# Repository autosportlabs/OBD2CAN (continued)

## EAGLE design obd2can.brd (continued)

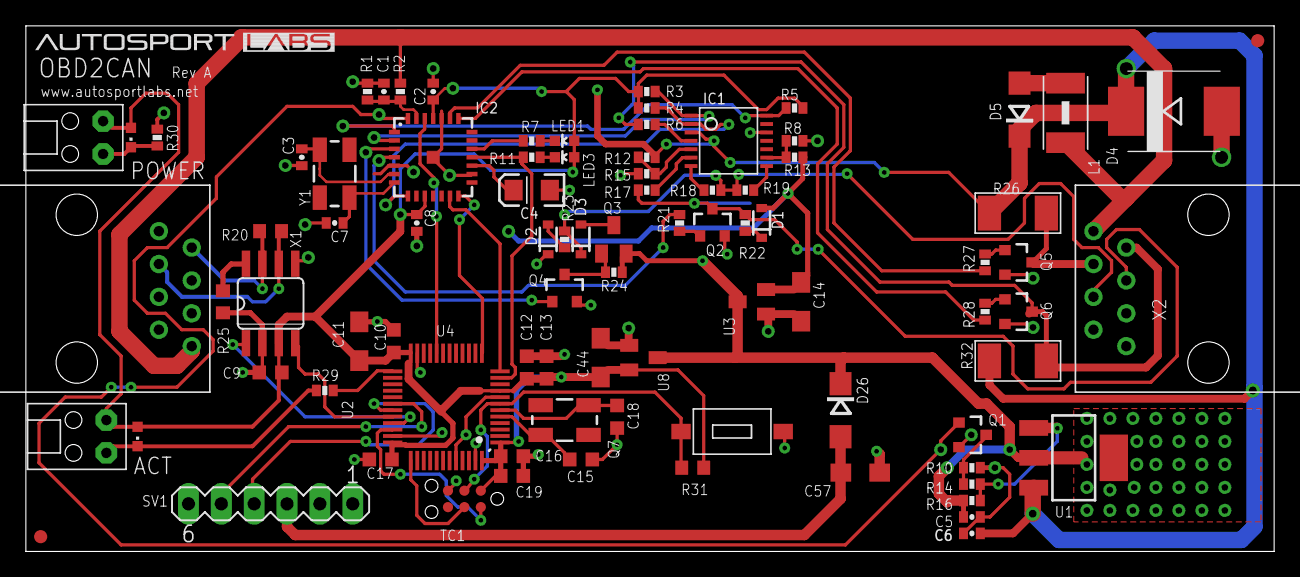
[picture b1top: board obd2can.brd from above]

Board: 2 copper layers, 96.5 x 40.6 mm, 85 parts (0 on the bottom side), 61 nets.

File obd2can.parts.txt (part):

Partlist


EAGLE Version 7.2.0 Copyright (c) 1988-2014 CadSoft

Assembly variant: 

Part     Value                            Device                           Package                           Library           Sheet

ACT      PANEL_LED                        PANEL_LED                        RIGHTANGLE_CML_5323F5             LEDs              1
ACT_S                                     LEDCHIPLED_0603                  CHIPLED_0603                      led               1
C1       0.1uF                            CAP0402-CAP                      0402-CAP                          SparkFun          3
C2       1uF                              CAP0402-CAP                      0402-CAP                          SparkFun          3
C3       27pF                             CAP0402-CAP                      0402-CAP                          SparkFun          3
C4       10uF ESR<=5                      CAP_POL1206                      EIA3216                           SparkFun          3
C5       1uF                              CAP0402-CAP                      0402-CAP                          SparkFun          2
C6       0.1uF                            CAP0402-CAP                      0402-CAP                          SparkFun          2
C7       27pF                             CAP0402-CAP                      0402-CAP                          SparkFun          3
C8       1uF                              CAP0402-CAP                      0402-CAP                          SparkFun          3
C9       0.1uf                            C-USC0603K                       C0603K                            rcl               1
C10      0.1uf                            C-USC0603K                       C0603K                            rcl               1
C11      10uF                             CPOL-USSMCA                      SMC_A                             rcl               1
C12      4.7uf                            C-USC0603K                       C0603K                            rcl               1
C13      0.01uf                           C-USC0603K                       C0603K                            rcl               1
C14      10uF                             CPOL-USSMCA                      SMC_A                             rcl               2
C15      0.1uf                            C-USC0603K                       C0603K                            rcl               1
C16      0.1uf                            C-USC0603K                       C0603K                            rcl               1
C17      4.7uf                            C-USC0603K                       C0603K                            rcl               1
C18      0.1uf                            C-USC0603K                       C0603K                            rcl               1
C19      1uf                              C-USC0603K                       C0603K                            rcl               1
C44      10uF                             CPOL-USSMCA                      SMC_A                             rcl               2
C57      10uF                             CPOL-USSMCA                      SMC_A                             rcl               1
D1       BAS16                            DIODESOD                         SOD-323                           SparkFun          4
D2       BAS16                            DIODESOD                         SOD-323                           SparkFun          4
D3       BAS16                            DIODESOD                         SOD-323                           SparkFun          4
D4                                        SCHOTTKY-DIODESMC                SMC                               diode             2
D5       400V 1A                          DIODE1                           SMA                               smt_diodes        2
D26      SCHOTTKY                         SCHOTTKY                         SMA                               smt_diodes        1
IC1      LM339PWR                         LM339PWR                         TSSOP-14                          _stn_logic        4
IC2      SCANTOOL                         SCANTOOL                         _STN_SCANTOOL_QFN-28-S            SparkFun          3
L1                                        WE-CBF_1812                      1812                              wuerth-elektronik 2
LED1     YELLOW                           LED0603                          LED-0603                          SparkFun          3
LED3     RED                              LED0603                          LED-0603                          SparkFun          3
POWER    PANEL_LED                        PANEL_LED                        RIGHTANGLE_CML_5323F5             LEDs              2
POWER_S                                   LEDCHIPLED_0603                  CHIPLED_0603                      led               2
Q1       BSS138                           MOSFET-NCHANNELSMD               SOT23-3                           SparkFun          2
Q2       MMBT2222                         TRANSISTOR_NPNSOT23-3            SOT23-3                           SparkFun          4
Q3       ZXMP6A13FTA                      MOSFET-PCHANNEL                  SOT23                             SparkFun          4
Q4       BSS138                           MOSFET-NCHANNELSMD               SOT23-3                           SparkFun          4
Q5       MMBT2222                         TRANSISTOR_NPNSOT23-3            SOT23-3                           SparkFun          4
Q6       MMBT2222                         TRANSISTOR_NPNSOT23-3            SOT23-3                           SparkFun          4
Q7       8MHz                             CRYSTAL5X3                       CRYSTAL-SMD-5X3                   SparkFun2         1
R1       10K                              RESISTOR0402-RES                 0402-RES                          SparkFun          3
R2       62K                              RESISTOR0402-RES                 0402-RES                          SparkFun          3
R3       10k                              RESISTOR0402-RES                 0402-RES                          SparkFun          4
R4       10k                              RESISTOR0402-RES                 0402-RES                          SparkFun          4
R5       10k                              RESISTOR0402-RES                 0402-RES                          SparkFun          4
R6       10k                              RESISTOR0402-RES                 0402-RES                          SparkFun          4
R7       330                              RESISTOR0402-RES                 0402-RES                          SparkFun          3
R8       4.7k                             RESISTOR0402-RES                 0402-RES                          SparkFun          4
R10      374                              RESISTOR0402-RES                 0402-RES                          SparkFun          2
R11      330                              RESISTOR0402-RES                 0402-RES                          SparkFun          3
R12      10k                              RESISTOR0402-RES                 0402-RES                          SparkFun          4
R13      1.2k                             RESISTOR0402-RES                 0402-RES                          SparkFun          4
R14      866                              RESISTOR0402-RES                 0402-RES                          SparkFun          2
R15      10k                              RESISTOR0402-RES                 0402-RES                          SparkFun          4
R16      240                              RESISTOR0402-RES                 0402-RES                          SparkFun          2
R17      10k                              RESISTOR0402-RES                 0402-RES                          SparkFun          4
R18      10k                              RESISTOR0402-RES                 0402-RES                          SparkFun          4
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
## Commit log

2014-02-16 added initial files and license
2014-02-18 added swdebug and boot button
2014-02-18 minor label updates
2014-02-19 grounded vref pin on can transceiver
2014-05-14 added image
2014-05-14 updated readme with improved description and board screenshot
2015-06-05 OBD2CAN WIP
2015-06-06 combined designs together
2015-06-06 label adjustment, snapshot image
2015-06-09 OBD2CAN WIP - more air wires routed
2015-06-09 only 5 more airwires to route...
2015-06-09 fully routed; passes DRC and ERC
2015-06-09 added the ability to supply power via FTDI header
2015-06-11 Fixed typo
2015-06-25 add NVM_RST line between STM32 and STN chips
2015-06-25 updated board image
2015-06-26 Add script to render PNGs of schematics, boards, and part list
2015-06-26 fix palette in rendered images, link to correct board image in readme
2016-02-01 cleaned up old files
2016-02-01 upate readme
2016-07-12 removed obsolete CAD files
2016-07-12 updated ignore file
2016-07-12 initial firmware load
2016-07-13 WIP for talking to STN1110
2016-07-15 WIP, update ChibiOS, update STN1110 reset
2016-07-15 update new ChibiOS
2016-07-15 update license
2016-07-17 more updates
2016-07-17 add license
2016-08-29 WIP enabling CAN
2016-08-30 WIP for CAN
2016-08-31 tweak baud rate for 500K. may not be accurate b/c internal oscillator
2016-08-31 set message length
2016-08-31 minor refactoring
2016-08-31 beginnings of CAN command message handling
2016-08-31 refactored debug writing
2016-08-31 WIP receiving PID requests
2016-09-01 bare end-end functionality; very WIP
2016-09-01 correct PID translation into CAN
2016-09-01 major refactoring
2016-09-01 documentation.
2016-09-01 refactor serial initialization
2016-09-01 updated commenting
2016-09-01 pass through OBDII request transparently, allowing any PID or mode
2016-09-01 expand heap
2016-09-01 proper timing for CAN messages and delays
2016-09-01 enable HSE.. maybe?
2016-09-01 set runtime STN1110 baud rate
2016-09-02 added logging infrastructure and other refactoring
2016-09-02 removed unused file
2016-09-02 clarified control message
2016-09-02 added license headers
2016-09-02 removed unused files
2016-09-02 removed unsused files
2016-09-02 remove unused files
2016-09-02 formatting
2016-09-02 extracted magic values; documentation
2016-09-02 refactored thread creation
2016-09-02 added watchdog support; disabled for now
2016-09-02 handle invalid pids; add metrics for stn1110
2016-09-02 refactored logging
2016-09-02 update CAN control ID
2016-09-02 added more error handling and tracking
2016-09-02 controllable reset and protocol via can message
2016-09-02 enum for obdii protocols
2016-09-03 enabled adaptive timing and timeout parameters
2016-09-03 added stats broadcasting
2016-09-03 make DLC length for stats 8 bytes
2016-09-03 restore logging level
2016-09-03 key off of > prompt for returned data
2016-09-04 enable adaptive stretching of OBDII requests to accomodate slower protocols
2016-09-06 better detect BUS ??? ERROR messages
2016-09-06 cap max bytes in message to CAN message length - 1
2016-09-18 add brief logging and timestamp support
2016-09-18 switch to 250K baud for CAN
2016-09-18 refactored to have STN1110 pid request in STN1110.c
2016-09-18 detect protocol after first successful PID response; various other refactorings
2016-09-19 simplify error handling; reset system if there are excessive errors
2016-09-19 disable automatic CAN message re-transmit
2016-09-19 enhanced documentation
2016-09-19 update README with more documentation
2016-09-19 formatted with astyle --linux
2016-09-19 fix markdown
2016-09-19 update git ignore
2016-09-20 part 1 of refactoring / feedback
2016-09-20 refactored large methods into smaller; other improvements and refactoring
2016-09-20 applied styling
2016-09-20 fixed comment formatting
2016-09-21 additional comments
2016-11-13 incorporate suggested changes from PR
2016-11-13 add version information to diagnostic CAN message; update documentation
2016-11-14 add openocd cfg
2016-11-18 request PID from only one ECU, to prevent multiple responses
2016-11-20 add misc tools to aid debugging
2016-11-20 ignore build directory
2016-11-20 base diagnostic messages on logging level. trace = 1Hz; no logging = 0.1Hz
2016-11-20 output HSE clock on PA8
2016-11-20 switch to 500K clock
2016-11-20 added test script
2016-11-26 refine can baud prescalers for 500K baud
2016-11-27 set logging to none by default
2016-11-27 MC0 output to /8 to make measurement more manageable
2016-11-27 only send diag messages frequently if in trace mode
2016-11-27 added more test files to be instrumented by RCP
2016-11-28 make main loop finer grained
2017-08-07 Update README.md
    fix baud rate
2017-10-02 WIP migrating to STM32f042
2017-10-02 add invert logic for STN1110 voltage regulator
2019-12-11 STM32F042 WIP
2019-12-11 F042 WIP
2019-12-11 add new ChibiOS
2019-12-11 enable more debug
2019-12-11 f043 WIP
2019-12-11 update chibios
2019-12-11 042 WIP
2019-12-11 restore / remove debug code
2019-12-12 update baud rate, logging and version
2019-12-12 clean up code
2019-12-12 reduce logging
